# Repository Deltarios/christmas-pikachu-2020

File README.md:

# christmas-pikachu-2020
Diseño de PCB en forma de Pikachu para la navidad del 2020 para Open Hardware.

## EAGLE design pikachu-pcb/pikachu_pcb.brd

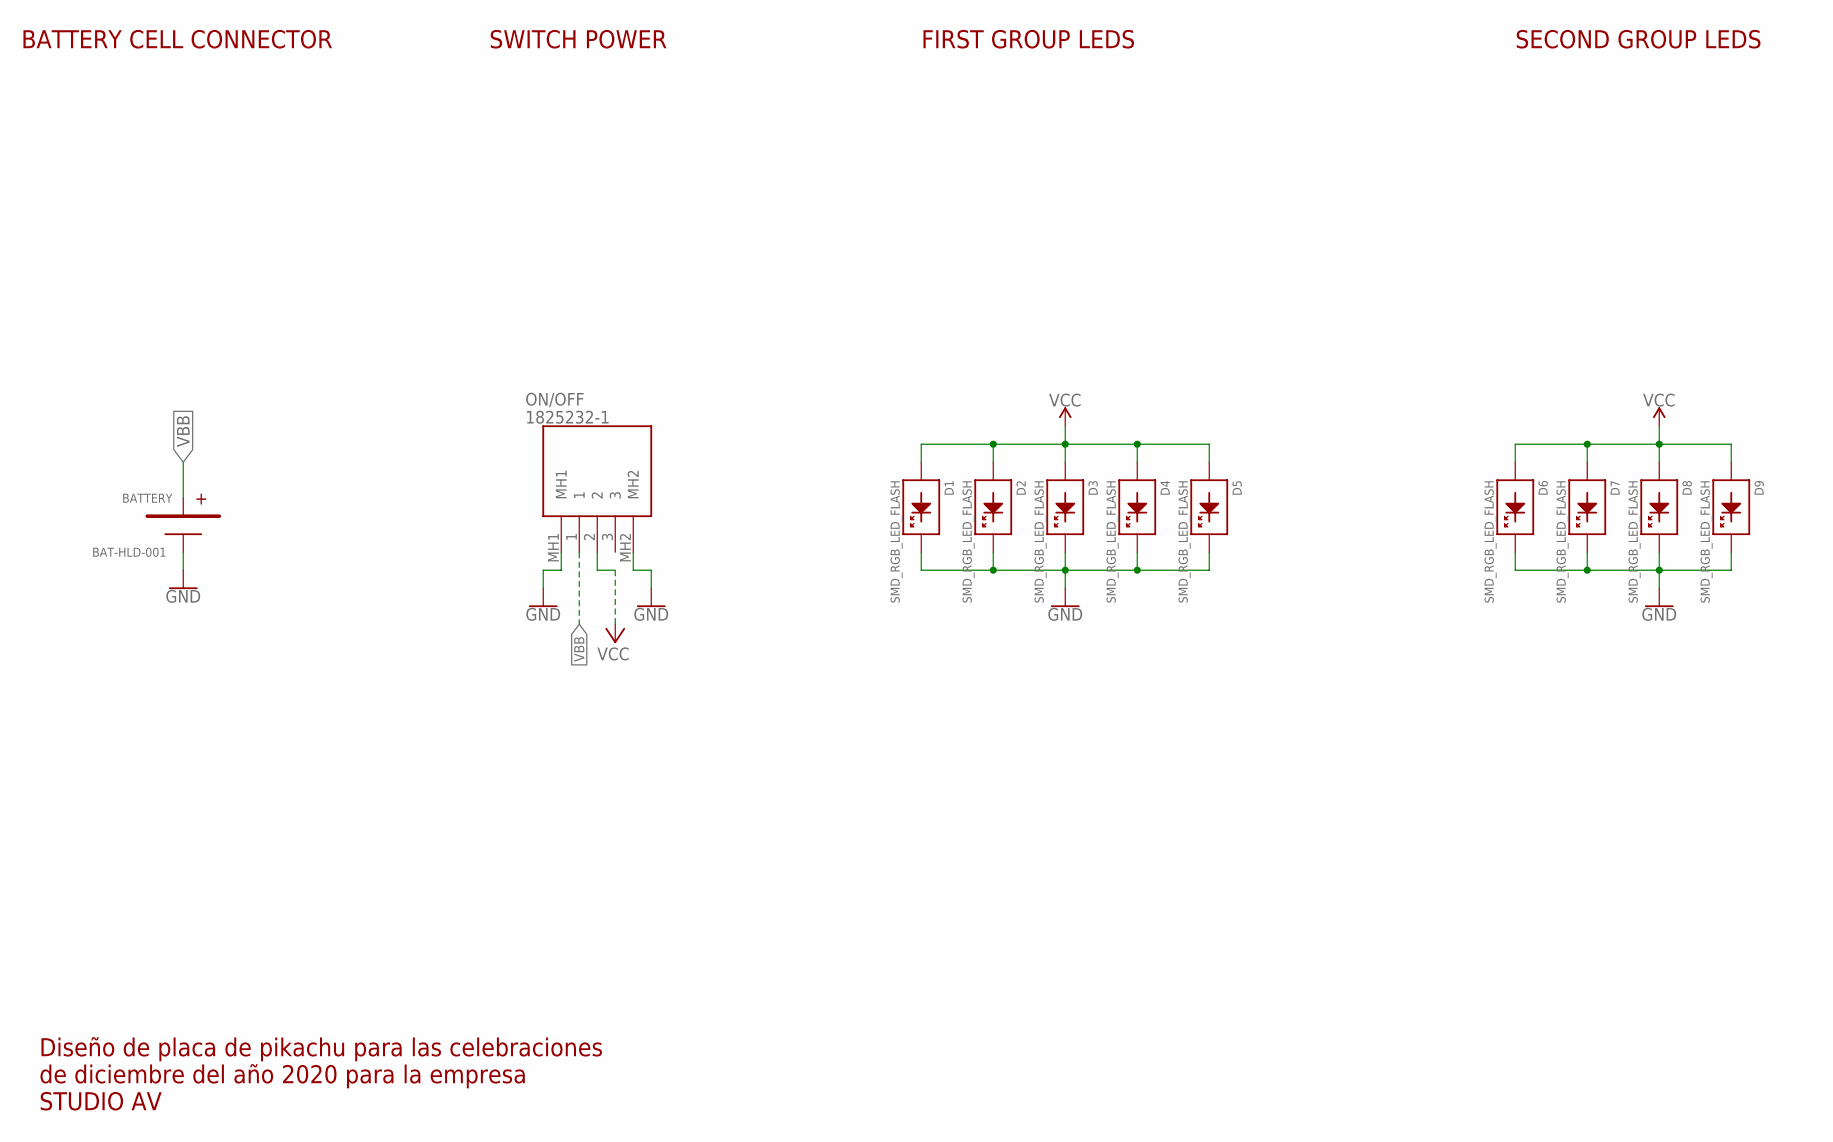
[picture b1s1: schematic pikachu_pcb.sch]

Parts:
BATTERY: BAT-HLD-001; BATHLD001
D1, D2, D3, D4, D5, D6, D7, D8, D9: SMD_RGB_LED_FLASH; SMD_RGB_LED_0807
ON/OFF: 1825232-1; 18252321

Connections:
GND: BATTERY.3 (N), D1.3 (K), D1.4 (K), D2.3 (K), D2.4 (K), D3.3 (K), D3.4 (K), D4.3 (K), D4.4 (K), D5.3 (K), D5.4 (K), D6.3 (K), D6.4 (K), D7.3 (K), D7.4 (K), D8.3 (K), D8.4 (K), D9.3 (K), D9.4 (K), ON/OFF.MH1
VBB: BATTERY.1, BATTERY.2, ON/OFF.1
VCC: D1.1 (A), D1.2 (A), D2.1 (A), D2.2 (A), D3.1 (A), D3.2 (A), D4.1 (A), D4.2 (A), D5.1 (A), D5.2 (A), D6.1 (A), D6.2 (A), D7.1 (A), D7.2 (A), D8.1 (A), D8.2 (A), D9.1 (A), D9.2 (A), ON/OFF.2

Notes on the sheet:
Diseño de placa de pikachu para las celebraciones de diciembre del año 2020 para la empresa STUDIO AV
BATTERY CELL CONNECTOR
SWITCH POWER
FIRST GROUP LEDS
SECOND GROUP LEDS

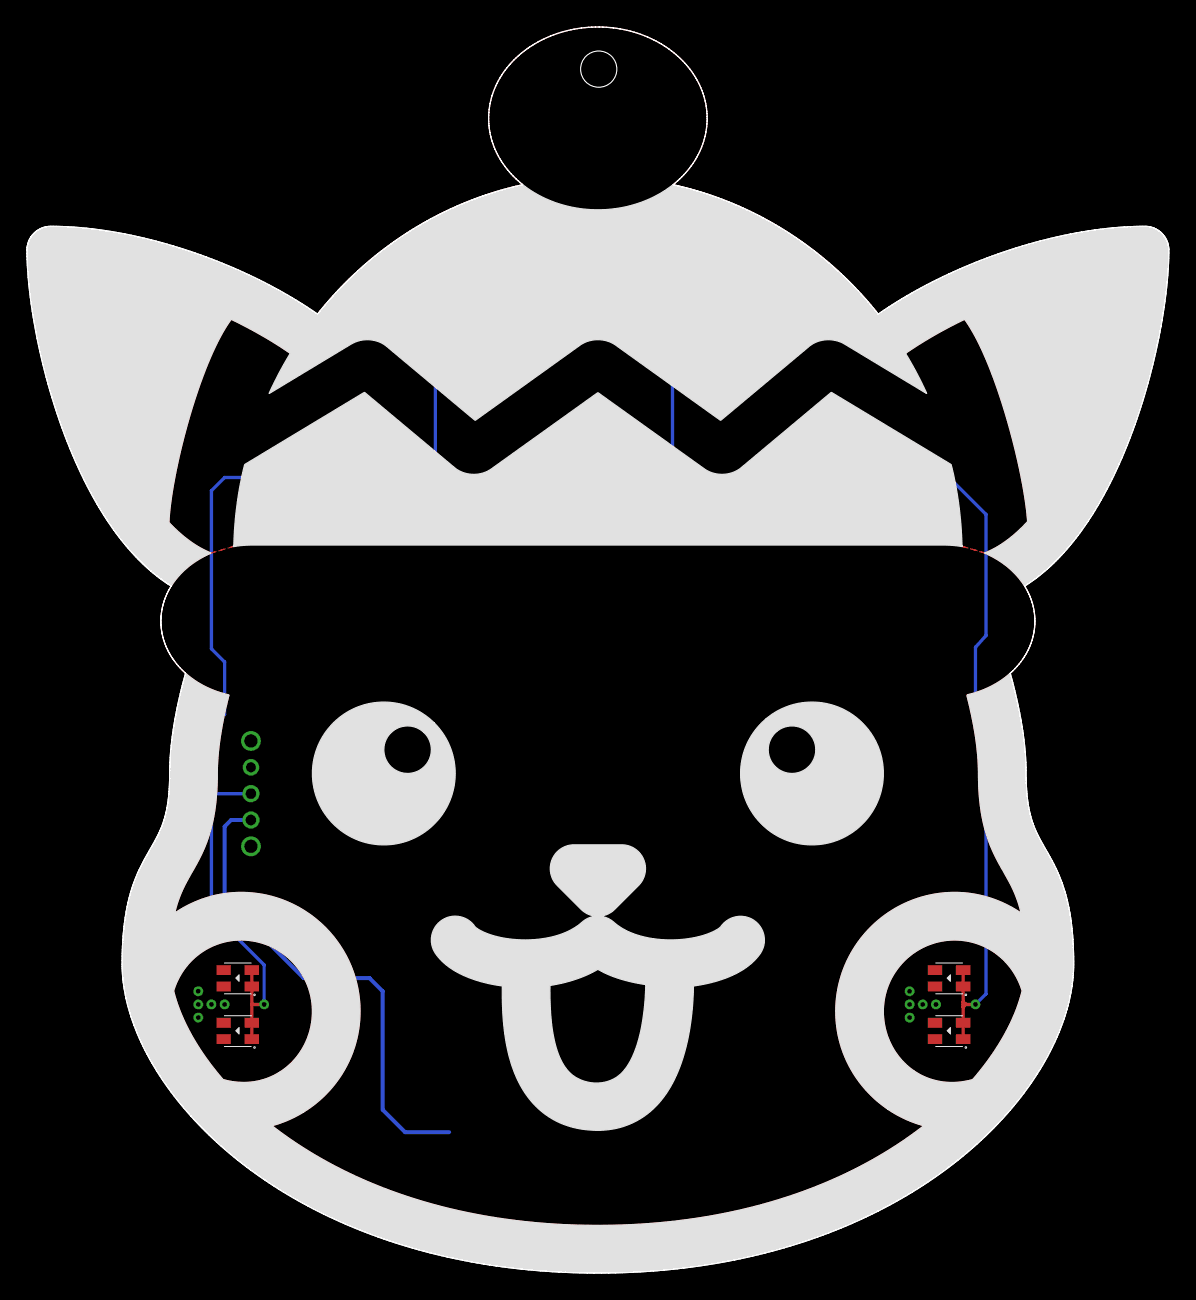
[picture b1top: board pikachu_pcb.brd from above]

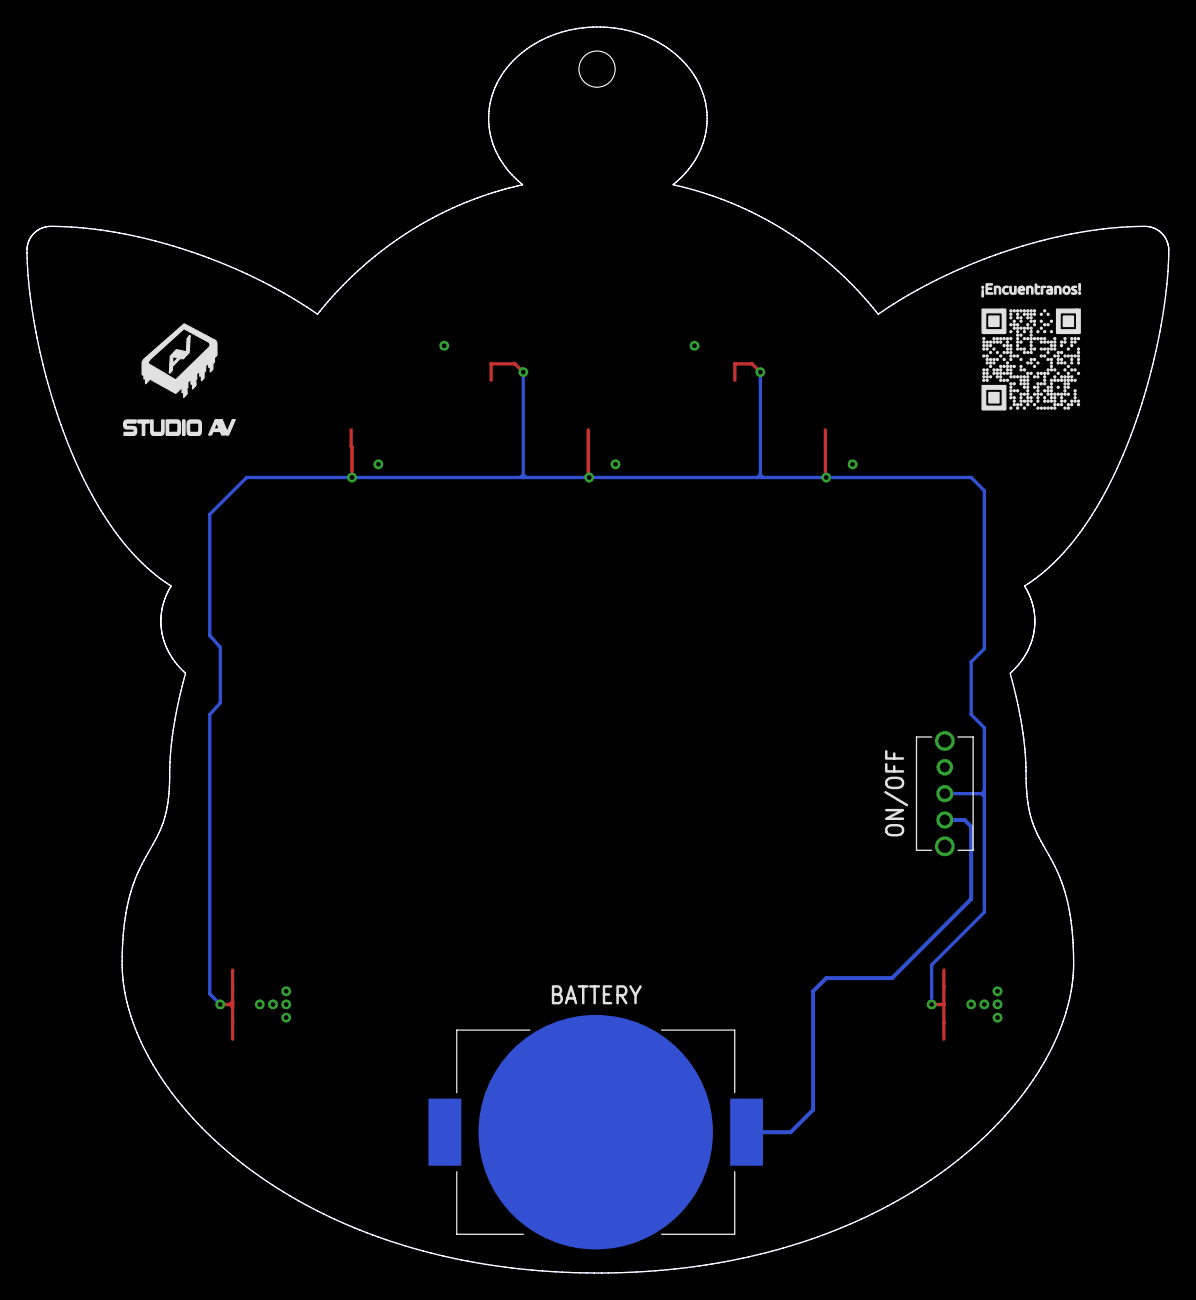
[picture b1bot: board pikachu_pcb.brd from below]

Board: 2 copper layers, 86.7 x 94.6 mm, 11 parts (2 on the bottom side), 3 nets.

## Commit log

2020-12-15 Inicio de proyecto
2020-12-15 Organizacion del proyecto
